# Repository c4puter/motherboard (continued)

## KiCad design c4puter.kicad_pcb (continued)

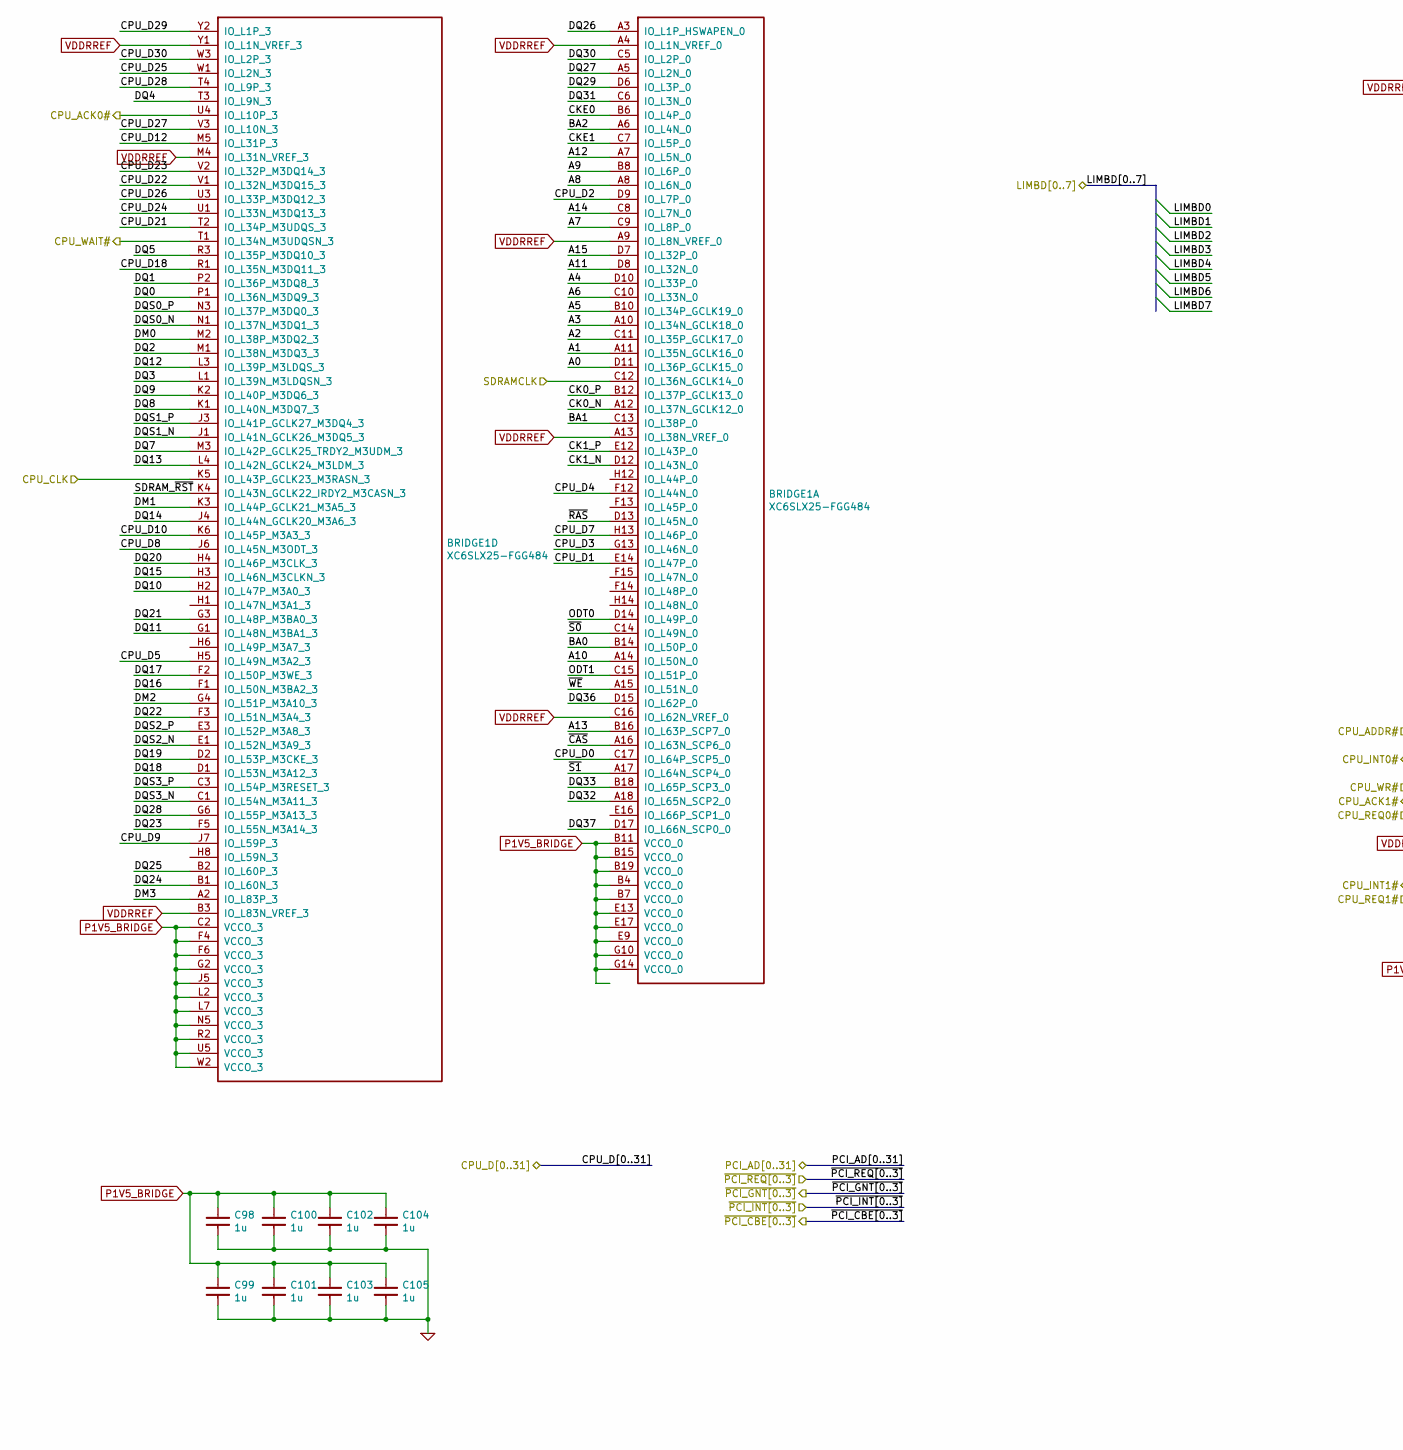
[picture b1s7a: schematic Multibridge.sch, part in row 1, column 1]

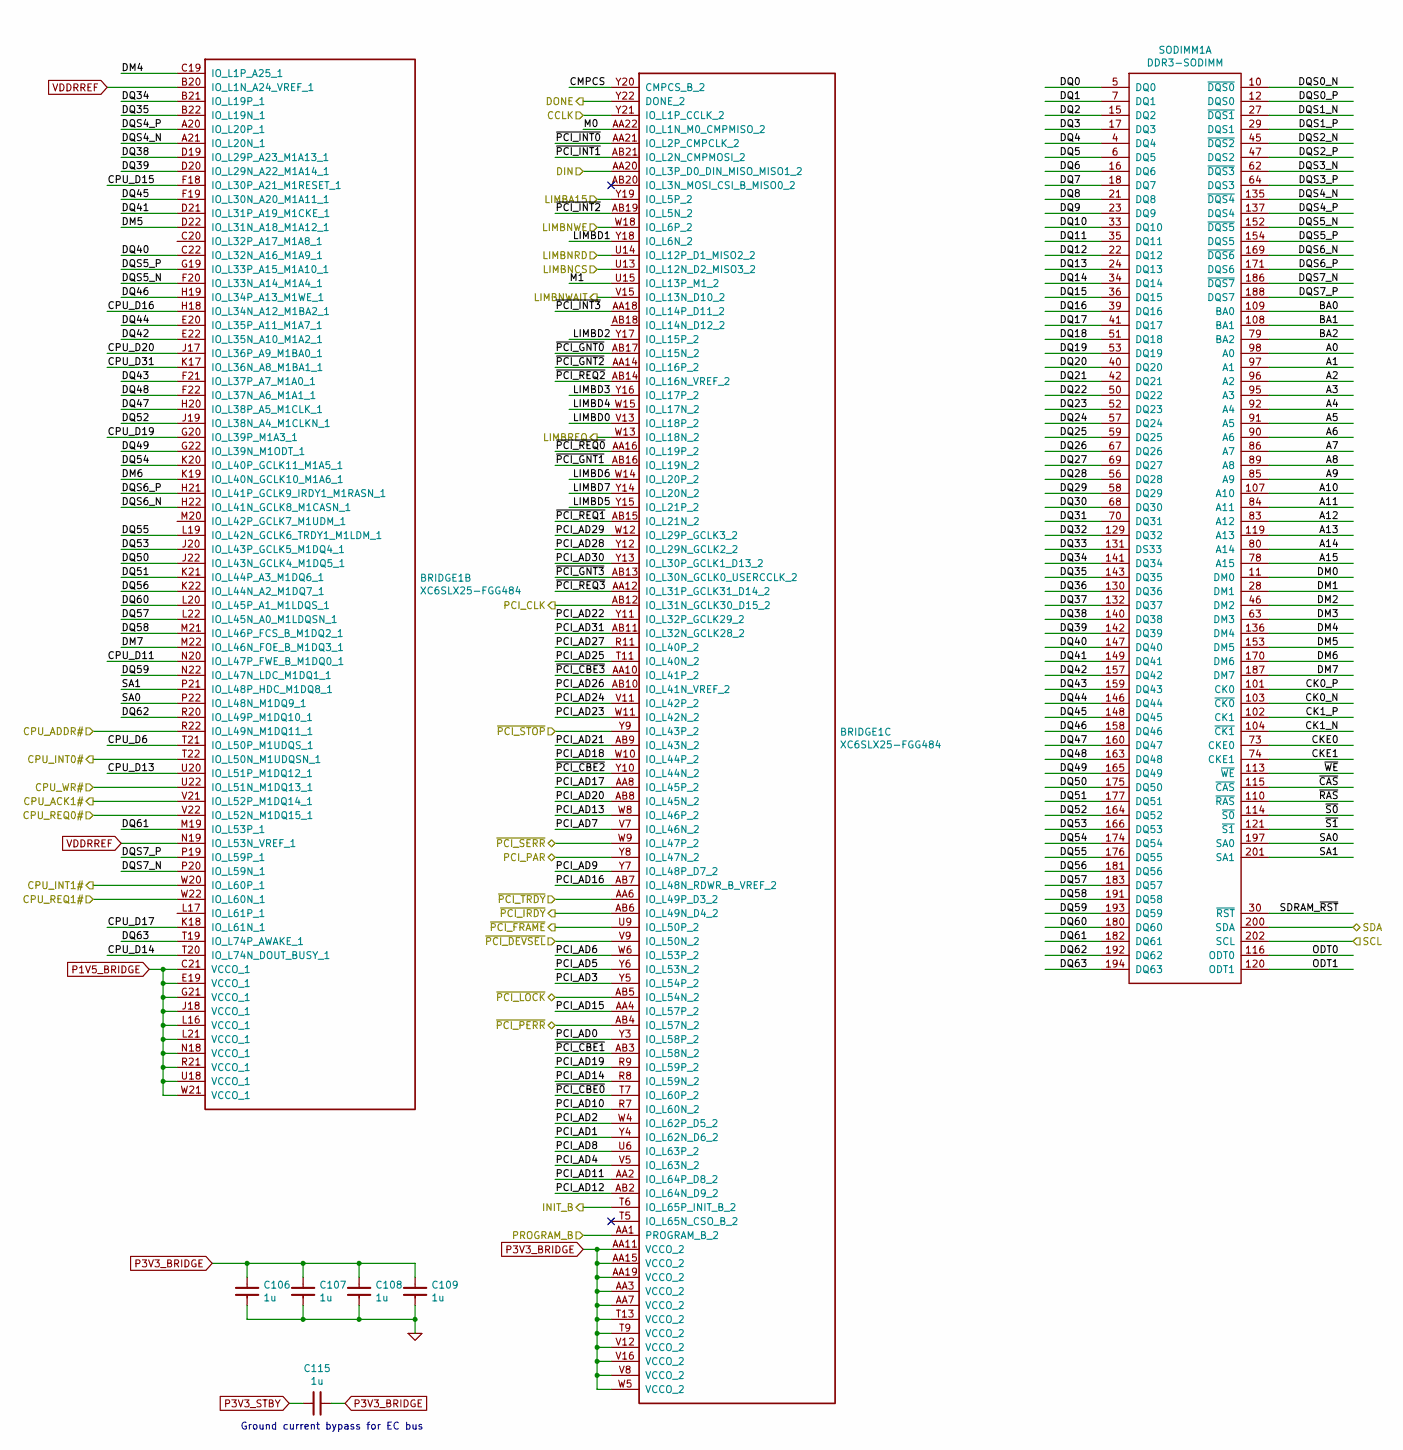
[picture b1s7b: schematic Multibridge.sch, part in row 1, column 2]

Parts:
BRIDGE1: XC6SLX25-FGG484; XILINX-FGG484
C98, C99, C100, C101, C102, C103, C104, C105, C106, C107, C108, C109, C115: 1u; CAPC1005X55
SODIMM1: DDR3-SODIMM

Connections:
/CPU0/ADDR#: BRIDGE1.R22 (IO_L49N_M1DQ11_1); also elsewhere on the board
/CPU0/BUSACK#: BRIDGE1.U4 (IO_L10P_3); also elsewhere on the board
/CPU0/BUSCLK: BRIDGE1.K5 (IO_L43P_GCLK23_M3RASN_3); also elsewhere on the board
/CPU0/BUSINT#: BRIDGE1.T22 (IO_L50N_M1UDQSN_1); also elsewhere on the board
/CPU0/BUSREQ#: BRIDGE1.V22 (IO_L52N_M1DQ15_1); also elsewhere on the board
/CPU0/CCLK: BRIDGE1.Y21 (IO_L1P_CCLK_2); also elsewhere on the board
/CPU0/DIN: BRIDGE1.AA20 (IO_L3P_D0_DIN_MISO_MISO1_2); also elsewhere on the board
/CPU0/INIT_B: BRIDGE1.T6 (IO_L65P_INIT_B_2); also elsewhere on the board
/CPU1/BUSACK#: BRIDGE1.V21 (IO_L52P_M1DQ14_1); also elsewhere on the board
/CPU1/BUSINT#: BRIDGE1.W20 (IO_L60P_1); also elsewhere on the board
/CPU1/BUSREQ#: BRIDGE1.W22 (IO_L60N_1); also elsewhere on the board
/EC/A15: BRIDGE1.Y19 (IO_L5P_2); also elsewhere on the board
/EC/D0: BRIDGE1.V13 (IO_L18P_2); also elsewhere on the board
/EC/D1: BRIDGE1.Y18 (IO_L6N_2); also elsewhere on the board
/EC/D2: BRIDGE1.Y17 (IO_L15P_2); also elsewhere on the board
/EC/D3: BRIDGE1.Y16 (IO_L17P_2); also elsewhere on the board
/EC/D4: BRIDGE1.W15 (IO_L17N_2); also elsewhere on the board
/EC/D5: BRIDGE1.Y15 (IO_L21P_2); also elsewhere on the board
/EC/D6: BRIDGE1.W14 (IO_L20P_2); also elsewhere on the board
/EC/D7: BRIDGE1.Y14 (IO_L20N_2); also elsewhere on the board
/Misc/CLK_SDRAM: BRIDGE1.C12 (IO_L36N_GCLK14_0); also elsewhere on the board
/Multibridge/A0: BRIDGE1.D11 (IO_L36P_GCLK15_0), SODIMM1.98 (A0)
/Multibridge/A1: BRIDGE1.A11 (IO_L35N_GCLK16_0), SODIMM1.97 (A1)
/Multibridge/A2: BRIDGE1.C11 (IO_L35P_GCLK17_0), SODIMM1.96 (A2)
/Multibridge/A3: BRIDGE1.A10 (IO_L34N_GCLK18_0), SODIMM1.95 (A3)
/Multibridge/A4: BRIDGE1.D10 (IO_L33P_0), SODIMM1.92 (A4)
/Multibridge/A5: BRIDGE1.B10 (IO_L34P_GCLK19_0), SODIMM1.91 (A5)
/Multibridge/A6: BRIDGE1.C10 (IO_L33N_0), SODIMM1.90 (A6)
/Multibridge/A7: BRIDGE1.C9 (IO_L8P_0), SODIMM1.86 (A7)
/Multibridge/A8: BRIDGE1.A8 (IO_L6N_0), SODIMM1.89 (A8)
/Multibridge/A9: BRIDGE1.B8 (IO_L6P_0), SODIMM1.85 (A9)
/Multibridge/A10: BRIDGE1.A14 (IO_L50N_0), SODIMM1.107 (A10)
/Multibridge/A11: BRIDGE1.D8 (IO_L32N_0), SODIMM1.84 (A11)
/Multibridge/A12: BRIDGE1.A7 (IO_L5N_0), SODIMM1.83 (A12)
/Multibridge/A13: BRIDGE1.B16 (IO_L63P_SCP7_0), SODIMM1.119 (A13)
/Multibridge/A14: BRIDGE1.C8 (IO_L7N_0), SODIMM1.80 (A14)
/Multibridge/A15: BRIDGE1.D7 (IO_L32P_0), SODIMM1.78 (A15)
/Multibridge/BA0: BRIDGE1.B14 (IO_L50P_0), SODIMM1.109 (BA0)
/Multibridge/BA1: BRIDGE1.C13 (IO_L38P_0), SODIMM1.108 (BA1)
/Multibridge/BA2: BRIDGE1.A6 (IO_L4N_0), SODIMM1.79 (BA2)
/Multibridge/CK0_N: BRIDGE1.A12 (IO_L37N_GCLK12_0), SODIMM1.103 (~CK0)
/Multibridge/CK0_P: BRIDGE1.B12 (IO_L37P_GCLK13_0), SODIMM1.101 (CK0)
/Multibridge/CK1_N: BRIDGE1.D12 (IO_L43N_0), SODIMM1.104 (~CK1)
/Multibridge/CK1_P: BRIDGE1.E12 (IO_L43P_0), SODIMM1.102 (CK1)
/Multibridge/CKE0: BRIDGE1.B6 (IO_L4P_0), SODIMM1.73 (CKE0)
/Multibridge/CKE1: BRIDGE1.C7 (IO_L5P_0), SODIMM1.74 (CKE1)
/Multibridge/CMPCS: BRIDGE1.Y20 (CMPCS_B_2)
/Multibridge/CPU_D0: BRIDGE1.C17 (IO_L64P_SCP5_0); also elsewhere on the board
/Multibridge/CPU_D1: BRIDGE1.E14 (IO_L47P_0); also elsewhere on the board
/Multibridge/CPU_D2: BRIDGE1.D9 (IO_L7P_0); also elsewhere on the board
/Multibridge/CPU_D3: BRIDGE1.G13 (IO_L46N_0); also elsewhere on the board
/Multibridge/CPU_D4: BRIDGE1.F12 (IO_L44N_0); also elsewhere on the board
/Multibridge/CPU_D5: BRIDGE1.H5 (IO_L49N_M3A2_3); also elsewhere on the board
/Multibridge/CPU_D6: BRIDGE1.T21 (IO_L50P_M1UDQS_1); also elsewhere on the board
/Multibridge/CPU_D7: BRIDGE1.H13 (IO_L46P_0); also elsewhere on the board
/Multibridge/CPU_D8: BRIDGE1.J6 (IO_L45N_M3ODT_3); also elsewhere on the board
/Multibridge/CPU_D9: BRIDGE1.J7 (IO_L59P_3); also elsewhere on the board
/Multibridge/CPU_D10: BRIDGE1.K6 (IO_L45P_M3A3_3); also elsewhere on the board
/Multibridge/CPU_D11: BRIDGE1.N20 (IO_L47P_FWE_B_M1DQ0_1); also elsewhere on the board
/Multibridge/CPU_D12: BRIDGE1.M5 (IO_L31P_3); also elsewhere on the board
/Multibridge/CPU_D13: BRIDGE1.U20 (IO_L51P_M1DQ12_1); also elsewhere on the board
/Multibridge/CPU_D14: BRIDGE1.T20 (IO_L74N_DOUT_BUSY_1); also elsewhere on the board
/Multibridge/CPU_D15: BRIDGE1.F18 (IO_L30P_A21_M1RESET_1); also elsewhere on the board
/Multibridge/CPU_D16: BRIDGE1.H18 (IO_L34N_A12_M1BA2_1); also elsewhere on the board
/Multibridge/CPU_D17: BRIDGE1.K18 (IO_L61N_1); also elsewhere on the board
/Multibridge/CPU_D18: BRIDGE1.R1 (IO_L35N_M3DQ11_3); also elsewhere on the board
/Multibridge/CPU_D19: BRIDGE1.G20 (IO_L39P_M1A3_1); also elsewhere on the board
/Multibridge/CPU_D20: BRIDGE1.J17 (IO_L36P_A9_M1BA0_1); also elsewhere on the board
/Multibridge/CPU_D21: BRIDGE1.T2 (IO_L34P_M3UDQS_3); also elsewhere on the board
/Multibridge/CPU_D22: BRIDGE1.V1 (IO_L32N_M3DQ15_3); also elsewhere on the board
/Multibridge/CPU_D23: BRIDGE1.V2 (IO_L32P_M3DQ14_3); also elsewhere on the board
/Multibridge/CPU_D24: BRIDGE1.U1 (IO_L33N_M3DQ13_3); also elsewhere on the board
/Multibridge/CPU_D25: BRIDGE1.W1 (IO_L2N_3); also elsewhere on the board
/Multibridge/CPU_D26: BRIDGE1.U3 (IO_L33P_M3DQ12_3); also elsewhere on the board
/Multibridge/CPU_D27: BRIDGE1.V3 (IO_L10N_3); also elsewhere on the board
/Multibridge/CPU_D28: BRIDGE1.T4 (IO_L9P_3); also elsewhere on the board
/Multibridge/CPU_D29: BRIDGE1.Y2 (IO_L1P_3); also elsewhere on the board
/Multibridge/CPU_D30: BRIDGE1.W3 (IO_L2P_3); also elsewhere on the board
/Multibridge/CPU_D31: BRIDGE1.K17 (IO_L36N_A8_M1BA1_1); also elsewhere on the board
/Multibridge/CPU_WAIT#: BRIDGE1.T1 (IO_L34N_M3UDQSN_3); also elsewhere on the board
/Multibridge/CPU_WR#: BRIDGE1.U22 (IO_L51N_M1DQ13_1); also elsewhere on the board
/Multibridge/DM0: BRIDGE1.M2 (IO_L38P_M3DQ2_3), SODIMM1.11 (DM0)
/Multibridge/DM1: BRIDGE1.K3 (IO_L44P_GCLK21_M3A5_3), SODIMM1.28 (DM1)
/Multibridge/DM2: BRIDGE1.G4 (IO_L51P_M3A10_3), SODIMM1.46 (DM2)
/Multibridge/DM3: BRIDGE1.A2 (IO_L83P_3), SODIMM1.63 (DM3)
/Multibridge/DM4: BRIDGE1.C19 (IO_L1P_A25_1), SODIMM1.136 (DM4)
/Multibridge/DM5: BRIDGE1.D22 (IO_L31N_A18_M1A12_1), SODIMM1.153 (DM5)
/Multibridge/DM6: BRIDGE1.K19 (IO_L40N_GCLK10_M1A6_1), SODIMM1.170 (DM6)
/Multibridge/DM7: BRIDGE1.M22 (IO_L46N_FOE_B_M1DQ3_1), SODIMM1.187 (DM7)
/Multibridge/DONE: BRIDGE1.Y22 (DONE_2); also elsewhere on the board
/Multibridge/DQ0: BRIDGE1.P1 (IO_L36N_M3DQ9_3), SODIMM1.5 (DQ0)
/Multibridge/DQ1: BRIDGE1.P2 (IO_L36P_M3DQ8_3), SODIMM1.7 (DQ1)
/Multibridge/DQ2: BRIDGE1.M1 (IO_L38N_M3DQ3_3), SODIMM1.15 (DQ2)
/Multibridge/DQ3: BRIDGE1.L1 (IO_L39N_M3LDQSN_3), SODIMM1.17 (DQ3)
/Multibridge/DQ4: BRIDGE1.T3 (IO_L9N_3), SODIMM1.4 (DQ4)
/Multibridge/DQ5: BRIDGE1.R3 (IO_L35P_M3DQ10_3), SODIMM1.6 (DQ5)
/Multibridge/DQ6: SODIMM1.16 (DQ6)
/Multibridge/DQ7: BRIDGE1.M3 (IO_L42P_GCLK25_TRDY2_M3UDM_3), SODIMM1.18 (DQ7)
/Multibridge/DQ8: BRIDGE1.K1 (IO_L40N_M3DQ7_3), SODIMM1.21 (DQ8)
/Multibridge/DQ9: BRIDGE1.K2 (IO_L40P_M3DQ6_3), SODIMM1.23 (DQ9)
/Multibridge/DQ10: BRIDGE1.H2 (IO_L47P_M3A0_3), SODIMM1.33 (DQ10)
/Multibridge/DQ11: BRIDGE1.G1 (IO_L48N_M3BA1_3), SODIMM1.35 (DQ11)
/Multibridge/DQ12: BRIDGE1.L3 (IO_L39P_M3LDQS_3), SODIMM1.22 (DQ12)
/Multibridge/DQ13: BRIDGE1.L4 (IO_L42N_GCLK24_M3LDM_3), SODIMM1.24 (DQ13)
/Multibridge/DQ14: BRIDGE1.J4 (IO_L44N_GCLK20_M3A6_3), SODIMM1.34 (DQ14)
/Multibridge/DQ15: BRIDGE1.H3 (IO_L46N_M3CLKN_3), SODIMM1.36 (DQ15)
/Multibridge/DQ16: BRIDGE1.F1 (IO_L50N_M3BA2_3), SODIMM1.39 (DQ16)
/Multibridge/DQ17: BRIDGE1.F2 (IO_L50P_M3WE_3), SODIMM1.41 (DQ17)
/Multibridge/DQ18: BRIDGE1.D1 (IO_L53N_M3A12_3), SODIMM1.51 (DQ18)
/Multibridge/DQ19: BRIDGE1.D2 (IO_L53P_M3CKE_3), SODIMM1.53 (DQ19)
/Multibridge/DQ20: BRIDGE1.H4 (IO_L46P_M3CLK_3), SODIMM1.40 (DQ20)
/Multibridge/DQ21: BRIDGE1.G3 (IO_L48P_M3BA0_3), SODIMM1.42 (DQ21)
/Multibridge/DQ22: BRIDGE1.F3 (IO_L51N_M3A4_3), SODIMM1.50 (DQ22)
/Multibridge/DQ23: BRIDGE1.F5 (IO_L55N_M3A14_3), SODIMM1.52 (DQ23)
/Multibridge/DQ24: BRIDGE1.B1 (IO_L60N_3), SODIMM1.57 (DQ24)
/Multibridge/DQ25: BRIDGE1.B2 (IO_L60P_3), SODIMM1.59 (DQ25)
/Multibridge/DQ26: BRIDGE1.A3 (IO_L1P_HSWAPEN_0), SODIMM1.67 (DQ26)
/Multibridge/DQ27: BRIDGE1.A5 (IO_L2N_0), SODIMM1.69 (DQ27)
/Multibridge/DQ28: BRIDGE1.G6 (IO_L55P_M3A13_3), SODIMM1.56 (DQ28)
/Multibridge/DQ29: BRIDGE1.D6 (IO_L3P_0), SODIMM1.58 (DQ29)
/Multibridge/DQ30: BRIDGE1.C5 (IO_L2P_0), SODIMM1.68 (DQ30)
/Multibridge/DQ31: BRIDGE1.C6 (IO_L3N_0), SODIMM1.70 (DQ31)
/Multibridge/DQ32: BRIDGE1.A18 (IO_L65N_SCP2_0), SODIMM1.129 (DQ32)
/Multibridge/DQ33: BRIDGE1.B18 (IO_L65P_SCP3_0), SODIMM1.131 (DS33)
/Multibridge/DQ34: BRIDGE1.B21 (IO_L19P_1), SODIMM1.141 (DQ34)
/Multibridge/DQ35: BRIDGE1.B22 (IO_L19N_1), SODIMM1.143 (DQ35)
/Multibridge/DQ36: BRIDGE1.D15 (IO_L62P_0), SODIMM1.130 (DQ36)
/Multibridge/DQ37: BRIDGE1.D17 (IO_L66N_SCP0_0), SODIMM1.132 (DQ37)
/Multibridge/DQ38: BRIDGE1.D19 (IO_L29P_A23_M1A13_1), SODIMM1.140 (DQ38)
/Multibridge/DQ39: BRIDGE1.D20 (IO_L29N_A22_M1A14_1), SODIMM1.142 (DQ39)
/Multibridge/DQ40: BRIDGE1.C22 (IO_L32N_A16_M1A9_1), SODIMM1.147 (DQ40)
/Multibridge/DQ41: BRIDGE1.D21 (IO_L31P_A19_M1CKE_1), SODIMM1.149 (DQ41)
/Multibridge/DQ42: BRIDGE1.E22 (IO_L35N_A10_M1A2_1), SODIMM1.157 (DQ42)
/Multibridge/DQ43: BRIDGE1.F21 (IO_L37P_A7_M1A0_1), SODIMM1.159 (DQ43)
/Multibridge/DQ44: BRIDGE1.E20 (IO_L35P_A11_M1A7_1), SODIMM1.146 (DQ44)
/Multibridge/DQ45: BRIDGE1.F19 (IO_L30N_A20_M1A11_1), SODIMM1.148 (DQ45)
/Multibridge/DQ46: BRIDGE1.H19 (IO_L34P_A13_M1WE_1), SODIMM1.158 (DQ46)
/Multibridge/DQ47: BRIDGE1.H20 (IO_L38P_A5_M1CLK_1), SODIMM1.160 (DQ47)
/Multibridge/DQ48: BRIDGE1.F22 (IO_L37N_A6_M1A1_1), SODIMM1.163 (DQ48)
/Multibridge/DQ49: BRIDGE1.G22 (IO_L39N_M1ODT_1), SODIMM1.165 (DQ49)
/Multibridge/DQ50: BRIDGE1.J22 (IO_L43N_GCLK4_M1DQ5_1), SODIMM1.175 (DQ50)
/Multibridge/DQ51: BRIDGE1.K21 (IO_L44P_A3_M1DQ6_1), SODIMM1.177 (DQ51)
/Multibridge/DQ52: BRIDGE1.J19 (IO_L38N_A4_M1CLKN_1), SODIMM1.164 (DQ52)
/Multibridge/DQ53: BRIDGE1.J20 (IO_L43P_GCLK5_M1DQ4_1), SODIMM1.166 (DQ53)
/Multibridge/DQ54: BRIDGE1.K20 (IO_L40P_GCLK11_M1A5_1), SODIMM1.174 (DQ54)
/Multibridge/DQ55: BRIDGE1.L19 (IO_L42N_GCLK6_TRDY1_M1LDM_1), SODIMM1.176 (DQ55)
/Multibridge/DQ56: BRIDGE1.K22 (IO_L44N_A2_M1DQ7_1), SODIMM1.181 (DQ56)
/Multibridge/DQ57: BRIDGE1.L22 (IO_L45N_A0_M1LDQSN_1), SODIMM1.183 (DQ57)
/Multibridge/DQ58: BRIDGE1.M21 (IO_L46P_FCS_B_M1DQ2_1), SODIMM1.191 (DQ58)
/Multibridge/DQ59: BRIDGE1.N22 (IO_L47N_LDC_M1DQ1_1), SODIMM1.193 (DQ59)
/Multibridge/DQ60: BRIDGE1.L20 (IO_L45P_A1_M1LDQS_1), SODIMM1.180 (DQ60)
/Multibridge/DQ61: BRIDGE1.M19 (IO_L53P_1), SODIMM1.182 (DQ61)
/Multibridge/DQ62: BRIDGE1.R20 (IO_L49P_M1DQ10_1), SODIMM1.192 (DQ62)
/Multibridge/DQ63: BRIDGE1.T19 (IO_L74P_AWAKE_1), SODIMM1.194 (DQ63)
/Multibridge/DQS0_N: BRIDGE1.N1 (IO_L37N_M3DQ1_3), SODIMM1.10 (~DQS0)
/Multibridge/DQS0_P: BRIDGE1.N3 (IO_L37P_M3DQ0_3), SODIMM1.12 (DQS0)
/Multibridge/DQS1_N: BRIDGE1.J1 (IO_L41N_GCLK26_M3DQ5_3), SODIMM1.27 (~DQS1)
/Multibridge/DQS1_P: BRIDGE1.J3 (IO_L41P_GCLK27_M3DQ4_3), SODIMM1.29 (DQS1)
/Multibridge/DQS2_N: BRIDGE1.E1 (IO_L52N_M3A9_3), SODIMM1.45 (~DQS2)
/Multibridge/DQS2_P: BRIDGE1.E3 (IO_L52P_M3A8_3), SODIMM1.47 (DQS2)
/Multibridge/DQS3_N: BRIDGE1.C1 (IO_L54N_M3A11_3), SODIMM1.62 (~DQS3)
/Multibridge/DQS3_P: BRIDGE1.C3 (IO_L54P_M3RESET_3), SODIMM1.64 (DQS3)
/Multibridge/DQS4_N: BRIDGE1.A21 (IO_L20N_1), SODIMM1.135 (~DQS4)
/Multibridge/DQS4_P: BRIDGE1.A20 (IO_L20P_1), SODIMM1.137 (DQS4)
/Multibridge/DQS5_N: BRIDGE1.F20 (IO_L33N_A14_M1A4_1), SODIMM1.152 (~DQS5)
/Multibridge/DQS5_P: BRIDGE1.G19 (IO_L33P_A15_M1A10_1), SODIMM1.154 (DQS5)
/Multibridge/DQS6_N: BRIDGE1.H22 (IO_L41N_GCLK8_M1CASN_1), SODIMM1.169 (~DQS6)
/Multibridge/DQS6_P: BRIDGE1.H21 (IO_L41P_GCLK9_IRDY1_M1RASN_1), SODIMM1.171 (DQS6)
/Multibridge/DQS7_N: BRIDGE1.P20 (IO_L59N_1), SODIMM1.186 (~DQS7)
/Multibridge/DQS7_P: BRIDGE1.P19 (IO_L59P_1), SODIMM1.188 (DQS7)
/Multibridge/LIMBNCS: BRIDGE1.U13 (IO_L12N_D2_MISO3_2); also elsewhere on the board
/Multibridge/LIMBNRD: BRIDGE1.U14 (IO_L12P_D1_MISO2_2); also elsewhere on the board
/Multibridge/LIMBNWAIT: BRIDGE1.V15 (IO_L13N_D10_2); also elsewhere on the board
/Multibridge/LIMBNWE: BRIDGE1.W18 (IO_L6P_2); also elsewhere on the board
/Multibridge/LIMBREQ: BRIDGE1.W13 (IO_L18N_2); also elsewhere on the board
/Multibridge/M0: BRIDGE1.AA22 (IO_L1N_M0_CMPMISO_2)
/Multibridge/M1: BRIDGE1.U15 (IO_L13P_M1_2)
/Multibridge/ODT0: BRIDGE1.D14 (IO_L49P_0), SODIMM1.116 (ODT0)
/Multibridge/ODT1: BRIDGE1.C15 (IO_L51P_0), SODIMM1.120 (ODT1)
/Multibridge/PROGRAM_B: BRIDGE1.AA1 (PROGRAM_B_2); also elsewhere on the board
/Multibridge/SA0: BRIDGE1.P22 (IO_L48N_M1DQ9_1), SODIMM1.197 (SA0)
/Multibridge/SA1: BRIDGE1.P21 (IO_L48P_HDC_M1DQ8_1), SODIMM1.201 (SA1)
/Multibridge/SCL: SODIMM1.202 (SCL); also elsewhere on the board
/Multibridge/SDA: SODIMM1.200 (SDA); also elsewhere on the board
/Multibridge/SDRAM_~RST: BRIDGE1.K4 (IO_L43N_GCLK22_IRDY2_M3CASN_3), SODIMM1.30 (~RST)
/Multibridge/~CAS: BRIDGE1.A16 (IO_L63N_SCP6_0), SODIMM1.115 (~CAS)
/Multibridge/~PCI_PERR: BRIDGE1.AB4 (IO_L57N_2); also elsewhere on the board
/Multibridge/~PCI_REQ0: BRIDGE1.AA16 (IO_L19P_2); also elsewhere on the board
/Multibridge/~PCI_REQ1: BRIDGE1.AB15 (IO_L21N_2); also elsewhere on the board
/Multibridge/~PCI_REQ2: BRIDGE1.AB14 (IO_L16N_VREF_2); also elsewhere on the board
/Multibridge/~PCI_REQ3: BRIDGE1.AA12 (IO_L31P_GCLK31_D14_2); also elsewhere on the board
/Multibridge/~PCI_SERR: BRIDGE1.W9 (IO_L47P_2); also elsewhere on the board
/Multibridge/~PCI_STOP: BRIDGE1.Y9 (IO_L43P_2); also elsewhere on the board
/Multibridge/~PCI_TRDY: BRIDGE1.AA6 (IO_L49P_D3_2); also elsewhere on the board
/Multibridge/~RAS: BRIDGE1.D13 (IO_L45N_0), SODIMM1.110 (~RAS)
/Multibridge/~S0: BRIDGE1.C14 (IO_L49N_0), SODIMM1.114 (~S0)
/Multibridge/~S1: BRIDGE1.A17 (IO_L64N_SCP4_0), SODIMM1.121 (~S1)
/Multibridge/~WE: BRIDGE1.A15 (IO_L51N_0), SODIMM1.113 (~WE)
/PCI/AD0: BRIDGE1.Y3 (IO_L58P_2); also elsewhere on the board
/PCI/AD1: BRIDGE1.Y4 (IO_L62N_D6_2); also elsewhere on the board
/PCI/AD2: BRIDGE1.W4 (IO_L62P_D5_2); also elsewhere on the board
/PCI/AD3: BRIDGE1.Y5 (IO_L54P_2); also elsewhere on the board
/PCI/AD4: BRIDGE1.V5 (IO_L63N_2); also elsewhere on the board
/PCI/AD5: BRIDGE1.Y6 (IO_L53N_2); also elsewhere on the board
/PCI/AD6: BRIDGE1.W6 (IO_L53P_2); also elsewhere on the board
/PCI/AD7: BRIDGE1.V7 (IO_L46N_2); also elsewhere on the board
/PCI/AD8: BRIDGE1.U6 (IO_L63P_2); also elsewhere on the board
/PCI/AD9: BRIDGE1.Y7 (IO_L48P_D7_2); also elsewhere on the board
/PCI/AD10: BRIDGE1.R7 (IO_L60N_2); also elsewhere on the board
/PCI/AD11: BRIDGE1.AA2 (IO_L64P_D8_2); also elsewhere on the board
/PCI/AD12: BRIDGE1.AB2 (IO_L64N_D9_2); also elsewhere on the board
/PCI/AD13: BRIDGE1.W8 (IO_L46P_2); also elsewhere on the board
/PCI/AD14: BRIDGE1.R8 (IO_L59N_2); also elsewhere on the board
/PCI/AD15: BRIDGE1.AA4 (IO_L57P_2); also elsewhere on the board
/PCI/AD16: BRIDGE1.AB7 (IO_L48N_RDWR_B_VREF_2); also elsewhere on the board
/PCI/AD17: BRIDGE1.AA8 (IO_L45P_2); also elsewhere on the board
/PCI/AD18: BRIDGE1.W10 (IO_L44P_2); also elsewhere on the board
/PCI/AD19: BRIDGE1.R9 (IO_L59P_2); also elsewhere on the board
/PCI/AD20: BRIDGE1.AB8 (IO_L45N_2); also elsewhere on the board
/PCI/AD21: BRIDGE1.AB9 (IO_L43N_2); also elsewhere on the board
/PCI/AD22: BRIDGE1.Y11 (IO_L32P_GCLK29_2); also elsewhere on the board
/PCI/AD23: BRIDGE1.W11 (IO_L42N_2); also elsewhere on the board
/PCI/AD24: BRIDGE1.V11 (IO_L42P_2); also elsewhere on the board
/PCI/AD25: BRIDGE1.T11 (IO_L40N_2); also elsewhere on the board
/PCI/AD26: BRIDGE1.AB10 (IO_L41N_VREF_2); also elsewhere on the board
/PCI/AD27: BRIDGE1.R11 (IO_L40P_2); also elsewhere on the board
/PCI/AD28: BRIDGE1.Y12 (IO_L29N_GCLK2_2); also elsewhere on the board
/PCI/AD29: BRIDGE1.W12 (IO_L29P_GCLK3_2); also elsewhere on the board
/PCI/AD30: BRIDGE1.Y13 (IO_L30P_GCLK1_D13_2); also elsewhere on the board
/PCI/AD31: BRIDGE1.AB11 (IO_L32N_GCLK28_2); also elsewhere on the board
/PCI/CLK: BRIDGE1.AB12 (IO_L31N_GCLK30_D15_2); also elsewhere on the board
/PCI/PAR: BRIDGE1.Y8 (IO_L47N_2); also elsewhere on the board
/PCI/~CBE0: BRIDGE1.T7 (IO_L60P_2); also elsewhere on the board
/PCI/~CBE1: BRIDGE1.AB3 (IO_L58N_2); also elsewhere on the board
/PCI/~CBE2: BRIDGE1.Y10 (IO_L44N_2); also elsewhere on the board
/PCI/~CBE3: BRIDGE1.AA10 (IO_L41P_2); also elsewhere on the board
/PCI/~DEVSEL: BRIDGE1.V9 (IO_L50N_2); also elsewhere on the board
/PCI/~FRAME: BRIDGE1.U9 (IO_L50P_2); also elsewhere on the board
/PCI/~GNT0: BRIDGE1.AB17 (IO_L15N_2); also elsewhere on the board
/PCI/~GNT1: BRIDGE1.AB16 (IO_L19N_2); also elsewhere on the board
/PCI/~GNT2: BRIDGE1.AA14 (IO_L16P_2); also elsewhere on the board
/PCI/~GNT3: BRIDGE1.AB13 (IO_L30N_GCLK0_USERCCLK_2); also elsewhere on the board
/PCI/~INT0: BRIDGE1.AA21 (IO_L2P_CMPCLK_2); also elsewhere on the board
/PCI/~INT1: BRIDGE1.AB21 (IO_L2N_CMPMOSI_2); also elsewhere on the board
/PCI/~INT2: BRIDGE1.AB19 (IO_L5N_2); also elsewhere on the board
/PCI/~INT3: BRIDGE1.AA18 (IO_L14P_D11_2); also elsewhere on the board
/PCI/~IRDY: BRIDGE1.AB6 (IO_L49N_D4_2); also elsewhere on the board
/PCI/~LOCK: BRIDGE1.AB5 (IO_L54N_2); also elsewhere on the board
GND: C98.2, C99.2, C100.2, C101.2, C102.2, C103.2, C104.2, C105.2, C106.2, C107.2, C108.2, C109.2; also elsewhere on the board
P1V5_BRIDGE: BRIDGE1.B4 (VCCO_0), BRIDGE1.B7 (VCCO_0), BRIDGE1.B11 (VCCO_0), BRIDGE1.B15 (VCCO_0), BRIDGE1.B19 (VCCO_0), BRIDGE1.C2 (VCCO_3), BRIDGE1.C21 (VCCO_1), BRIDGE1.E9 (VCCO_0), BRIDGE1.E13 (VCCO_0), BRIDGE1.E17 (VCCO_0), BRIDGE1.E19 (VCCO_1), BRIDGE1.F4 (VCCO_3), BRIDGE1.F6 (VCCO_3), BRIDGE1.G2 (VCCO_3), BRIDGE1.G10 (VCCO_0), BRIDGE1.G14 (VCCO_0), BRIDGE1.G21 (VCCO_1), BRIDGE1.J5 (VCCO_3), BRIDGE1.J18 (VCCO_1), BRIDGE1.L2 (VCCO_3), BRIDGE1.L7 (VCCO_3), BRIDGE1.L16 (VCCO_1), BRIDGE1.L21 (VCCO_1), BRIDGE1.N5 (VCCO_3), BRIDGE1.N18 (VCCO_1), BRIDGE1.R2 (VCCO_3), BRIDGE1.R21 (VCCO_1), BRIDGE1.U5 (VCCO_3), BRIDGE1.U18 (VCCO_1), BRIDGE1.W2 (VCCO_3), BRIDGE1.W21 (VCCO_1), C98.1, C99.1, C100.1, C101.1, C102.1, C103.1, C104.1, C105.1; also elsewhere on the board
P3V3_BRIDGE: BRIDGE1.AA3 (VCCO_2), BRIDGE1.AA7 (VCCO_2), BRIDGE1.AA11 (VCCO_2), BRIDGE1.AA15 (VCCO_2), BRIDGE1.AA19 (VCCO_2), BRIDGE1.T9 (VCCO_2), BRIDGE1.T13 (VCCO_2), BRIDGE1.V8 (VCCO_2), BRIDGE1.V12 (VCCO_2), BRIDGE1.V16 (VCCO_2), BRIDGE1.W5 (VCCO_2), C106.1, C107.1, C108.1, C109.1, C115.1; also elsewhere on the board
P3V3_STBY: C115.2; also elsewhere on the board
VDDRREF: BRIDGE1.A4 (IO_L1N_VREF_0), BRIDGE1.A9 (IO_L8N_VREF_0), BRIDGE1.A13 (IO_L38N_VREF_0), BRIDGE1.B3 (IO_L83N_VREF_3), BRIDGE1.B20 (IO_L1N_A24_VREF_1), BRIDGE1.C16 (IO_L62N_VREF_0), BRIDGE1.M4 (IO_L31N_VREF_3), BRIDGE1.N19 (IO_L53N_VREF_1), BRIDGE1.Y1 (IO_L1N_VREF_3)

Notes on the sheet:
Ground current bypass for EC bus

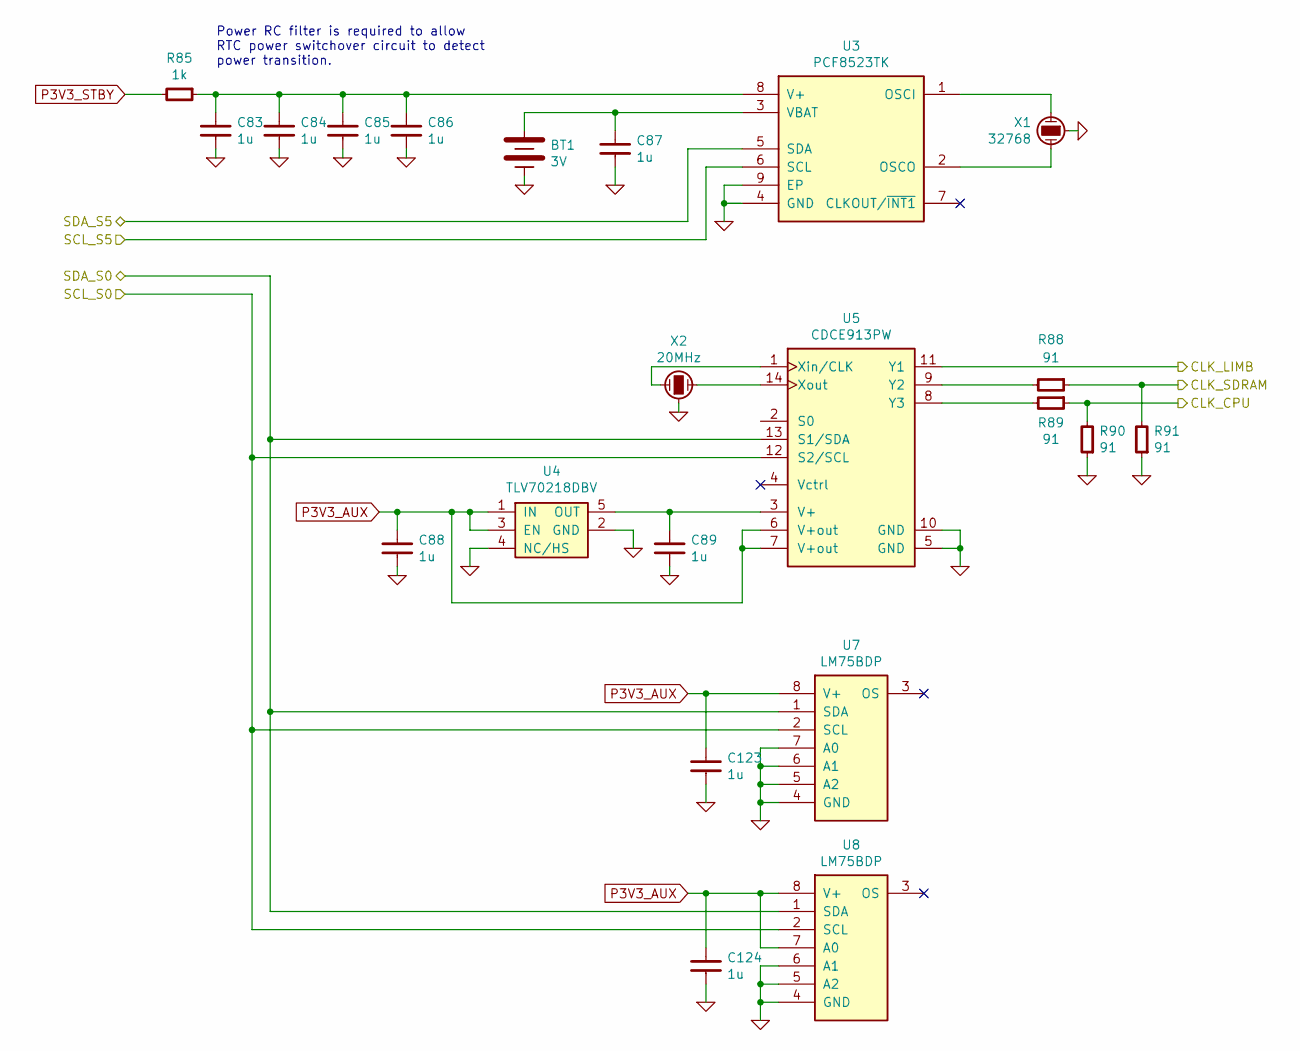
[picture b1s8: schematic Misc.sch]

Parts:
BT1: 3V; MPD-BU2032SM-HD-G
C83, C84, C85, C86, C87, C88, C89, C123, C124: 1u; CAPC1005X55
R85: 1k; RESC1005X40
R88, R89, R90, R91: 91; RESC1005X40
U3: PCF8523TK; SON80P400X400X80-9
U4: TLV70218DBV; SOT-23-5
U5: CDCE913PW; SOP65P640X120-14
U7, U8: LM75BDP; SOP65P490X110-8
X1: 32768; CITIZEN-CM130
X2: 20MHz; ABRACON-ABM8G

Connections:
/Blinkenlights/SCL: U3.6 (SCL); also elsewhere on the board
/Blinkenlights/SDA: U3.5 (SDA); also elsewhere on the board
/CPU0/BUSCLK: R89.1, R90.2; also elsewhere on the board
/EC/CLK: U5.11 (Y1); also elsewhere on the board
/Misc/CLK_SDRAM: R88.1, R91.2; also elsewhere on the board
/Multibridge/SCL: U5.12 (S2/SCL), U7.2 (SCL), U8.2 (SCL); also elsewhere on the board
/Multibridge/SDA: U5.13 (S1/SDA), U7.1 (SDA), U8.1 (SDA); also elsewhere on the board
GND: BT1.2 (-), C83.2, C84.2, C85.2, C86.2, C87.2, C88.2, C89.2, C123.2, C124.2, R90.1, R91.1, U3.4 (GND), U3.9 (EP), U4.2 (GND), U4.4 (NC/HS), U5.5 (GND), U5.10 (GND), U7.4 (GND), U7.5 (A2), U7.6 (A1), U7.7 (A0), U8.4 (GND), U8.5 (A2), U8.6 (A1), X1.3, X2.3; also elsewhere on the board
unnamed: BT1.1 (+), C87.1, U3.3 (VBAT)
unnamed: C83.1, C84.1, C85.1, C86.1, R85.1, U3.8 (V+)
unnamed: C89.1, U4.5 (OUT), U5.3 (V+)
unnamed: R88.2, U5.9 (Y2)
unnamed: R89.2, U5.8 (Y3)
unnamed: U3.1 (OSCI), X1.1
unnamed: U3.2 (OSCO), X1.2
unnamed: U5.1 (Xin/CLK), X2.1
unnamed: U5.14 (Xout), X2.2
P3V3_AUX: C88.1, C123.1, C124.1, U4.1 (IN), U4.3 (EN), U5.6 (V+out), U5.7 (V+out), U7.8 (V+), U8.7 (A0), U8.8 (V+); also elsewhere on the board
P3V3_STBY: R85.2; also elsewhere on the board

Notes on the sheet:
Power RC filter is required to allow RTC power switchover circuit to detect power transition.

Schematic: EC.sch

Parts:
C9, C125, C126, C127, C128, C129: 100n; CAPC1005X55
C130: 4u7; CAPC3216X70
J2: MICROSD; AMPHENOL-114-00841-68
J6: DEBUG; CONN-100MIL-M-2x5-SHROUD
J8: DEBUG; CONN-10118194-0001LF-FCI
J10: RS232
LIMB1: ATSAM4S16CA-AU; QFP50P1600X1600X160-100
M1: FAN-4PIN; CONN-100MIL-M-1x4-SHROUD
Q12, Q13, Q20, Q21: FK3303010L; PANASONIC-SSSMini3-F2-B
R3, R8, R9, R55, R86, R95, R96, R97: 5k1; RESC1005X40
R4: 100k; RESC1005X40
R17: 24; RESC1005X40
R56: 100k; RESC1608X50
R87, R92, R93, R94: 22V; RESC1608X50
SW3: SW-DIP-4; DIP-8
U9, U11: NUF2042XV6; SOT-563
U10: MAX3232PW; SOP65P640X140-16
W6, W7: NET-TIE; NET-TIE-0.2mm

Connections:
3V3_CARD: C9.2, J2.4, R56.1
/Blinkenlights/SCL: LIMB1.55 (PA4), Q13.3, R9.2; also elsewhere on the board
/Blinkenlights/SDA: LIMB1.66 (PA3), Q12.3, R8.2; also elsewhere on the board
/CPU0/CCLK: LIMB1.31 (PA14); also elsewhere on the board
/CPU0/DIN: R17.2; also elsewhere on the board
/CPU0/DONE: LIMB1.49 (PA7); also elsewhere on the board
/CPU0/INIT_B: LIMB1.53 (PA5); also elsewhere on the board
/CPU0/PROGRAM_B: LIMB1.46 (PA9); also elsewhere on the board
/CPU1/DONE: LIMB1.52 (PA6); also elsewhere on the board
/CPU1/PROGRAM_B: LIMB1.44 (PA10); also elsewhere on the board
/EC/A0: LIMB1.78 (PC18)
/EC/A7: LIMB1.94 (PC25)
/EC/A8: LIMB1.13 (PC26)
/EC/A9: LIMB1.17 (PC27)
/EC/A10: LIMB1.54 (PC28)
/EC/A11: LIMB1.4 (PC29)
/EC/A12: LIMB1.6 (PC30)
/EC/A13: LIMB1.8 (PC31)
/EC/A14: LIMB1.14 (PA18)
/EC/A15: LIMB1.18 (PA19); also elsewhere on the board
/EC/A16: LIMB1.24 (PA20)
/EC/A17: LIMB1.74 (PA0)
/EC/A22: LIMB1.75 (PC17)
/EC/CARD_DET#: J2.10 (CD2), R56.2
/EC/CLK: LIMB1.97 (PB9); also elsewhere on the board
/EC/CTS1: LIMB1.38 (PA25), U10.9 (ROUT2)
/EC/D0: LIMB1.25 (PC0); also elsewhere on the board
/EC/D1: LIMB1.47 (PC1); also elsewhere on the board
/EC/D2: LIMB1.43 (PC2); also elsewhere on the board
/EC/D3: LIMB1.40 (PC3); also elsewhere on the board
/EC/D4: LIMB1.37 (PC4); also elsewhere on the board
/EC/D5: LIMB1.35 (PC5); also elsewhere on the board
/EC/D6: LIMB1.32 (PC6); also elsewhere on the board
/EC/D7: LIMB1.29 (PC7); also elsewhere on the board
/EC/FANPWM: LIMB1.22 (PA23), U11.4
/EC/FANTACH: LIMB1.30 (PA15), R95.2, U11.6
/EC/MCCDA: J2.3, LIMB1.59 (PA28)
/EC/MCCK: J2.5, LIMB1.63 (PA29)
/EC/MCDA0: J2.7, LIMB1.64 (PA30)
/EC/MCDA1: J2.8, LIMB1.81 (PA31)
/EC/MCDA2: J2.1, LIMB1.39 (PA26)
/EC/MCDA3: J2.2, LIMB1.57 (PA27)
/EC/MISO: LIMB1.41 (PA12)
/EC/MOSI: LIMB1.33 (PA13), R17.1
/EC/NCS1: LIMB1.19 (PC15)
/EC/NCS3: LIMB1.23 (PC12)
/EC/OUT_USB1_D+: J8.3 (D+), U9.3
/EC/OUT_USB1_D-: J8.2 (D-), U9.1
/EC/PCI_SCL: Q21.2, R97.2; also elsewhere on the board
/EC/PCI_SDA: Q20.2, R96.2; also elsewhere on the board
/EC/RSCTS: J10.8, R93.1, U10.8 (RIN2)
/EC/RSDCD: J10.1
/EC/RSDSR: J10.6
/EC/RSDTR: J10.4
/EC/RSRD: J10.2, R87.1, U10.13 (RIN1)
/EC/RSRI: J10.9
/EC/RSRTS: J10.7, R94.1, U10.7 (DOUT2)
/EC/RSTD: J10.3, R92.1, U10.14 (DOUT1)
/EC/RTS1: LIMB1.34 (PA24), U10.10 (DIN2)
/EC/RXD1: LIMB1.15 (PA21), U10.12 (ROUT1)
/EC/SCK1: LIMB1.76 (PB5/TDO), Q21.3, W7.1
/EC/SDA1: LIMB1.51 (PB4/TDI), Q20.3, W6.1
/EC/TCK: J6.4, LIMB1.83 (PB7/TCK)
/EC/TDI: J6.8, W6.2
/EC/TDO: J6.6, W7.2
/EC/TMS: J6.2, LIMB1.79 (PB6/TMS)
/EC/TXD1: LIMB1.20 (PA22), U10.11 (DIN1)
/EC/USB_D+: LIMB1.89 (PB11/DDP), U9.4
/EC/USB_D-: LIMB1.88 (PB10/DDM), U9.6
/EC/USB_VBUS: R4.1
/EC/XFANPWM: M1.4 (PWM), U11.3
/EC/XFANTACH: M1.3 (TACH), U11.1
/EC/XOUT: LIMB1.96 (PB8)
/EC/~PCIPME: LIMB1.90 (PC23); also elsewhere on the board
/EC/~PCIRST: LIMB1.86 (PC22); also elsewhere on the board
/EC/~PRSNT1_0: LIMB1.84 (PC21); also elsewhere on the board
/EC/~PRSNT1_1: LIMB1.73 (PC16); also elsewhere on the board
/EC/~PRSNT1_2: LIMB1.67 (PA2); also elsewhere on the board
/EC/~PRSNT1_3: LIMB1.62 (PC9); also elsewhere on the board
/EC/~PRSNT2_0: LIMB1.82 (PC20); also elsewhere on the board
/EC/~PRSNT2_1: LIMB1.80 (PC19); also elsewhere on the board
/EC/~PRSNT2_2: LIMB1.72 (PA1); also elsewhere on the board
/EC/~PRSNT2_3: LIMB1.65 (PC10); also elsewhere on the board
/EC/~RST: J6.10, LIMB1.60 (NRST)
/Multibridge/DONE: LIMB1.48 (PA8); also elsewhere on the board
/Multibridge/LIMBNCS: LIMB1.71 (PC14); also elsewhere on the board
/Multibridge/LIMBNRD: LIMB1.68 (PC11); also elsewhere on the board
/Multibridge/LIMBNWAIT: LIMB1.21 (PC13); also elsewhere on the board
/Multibridge/LIMBNWE: LIMB1.58 (PC8); also elsewhere on the board
/Multibridge/LIMBREQ: LIMB1.28 (PA16); also elsewhere on the board
/Multibridge/PROGRAM_B: LIMB1.42 (PA11); also elsewhere on the board
/Multibridge/SCL: Q13.2, R86.2; also elsewhere on the board
/Multibridge/SDA: Q12.2, R55.2; also elsewhere on the board
/PCI/M66EN: LIMB1.92 (PC24); also elsewhere on the board
GND: C9.1, C126.2, C128.1, C129.1, C130.2, J2.6, J2.9 (CD1), J2.11 (MP), J6.3, J6.5, J6.9, J8.5 (GND), J10.5, LIMB1.2 (GND), LIMB1.26 (GND), LIMB1.45 (GND), LIMB1.70 (GND), LIMB1.95 (GND), M1.1 (V-), R3.1, R87.2, R92.2, R93.2, R94.2, SW3.1, SW3.2, SW3.3, SW3.4, U9.2, U10.15 (GND), U11.2; also elsewhere on the board
unnamed: C125.1, U10.4 (C2+)
unnamed: C125.2, U10.5 (C2-)
unnamed: C126.1, U10.6 (V-)
unnamed: C127.1, U10.3 (C1-)
unnamed: C127.2, U10.1 (C1+)
unnamed: C128.2, U10.2 (V+)
unnamed: J8.1 (V+), R3.2, R4.2, U9.5
unnamed: LIMB1.11 (VDDOUT), LIMB1.16 (VCORE), LIMB1.36 (VCORE), LIMB1.56 (VCORE), LIMB1.85 (VCORE), LIMB1.100 (VPLL)
P3V3_AUX: Q12.1, Q13.1, Q20.1, Q21.1, R55.1, R86.1, R95.1, R96.1, R97.1, U11.5; also elsewhere on the board
P3V3_STBY: C129.2, J6.1, LIMB1.10 (VDDIN), LIMB1.27 (VIO), LIMB1.50 (VIO), LIMB1.69 (VIO), LIMB1.91 (VIO), LIMB1.98 (VIO), R8.1, R9.1, U10.16 (VCC); also elsewhere on the board
P12V_PCI: C130.1, M1.2 (V+); also elsewhere on the board
